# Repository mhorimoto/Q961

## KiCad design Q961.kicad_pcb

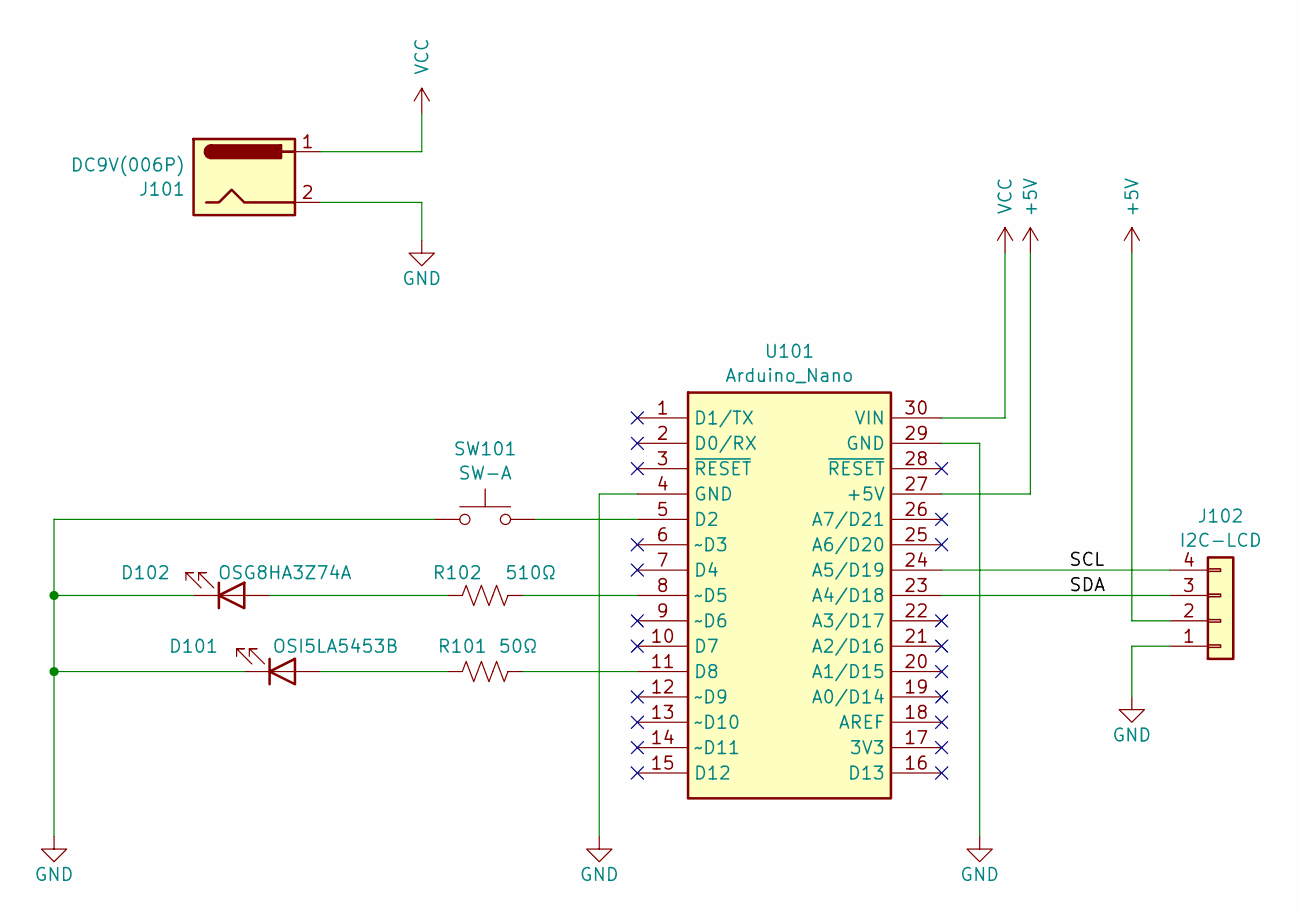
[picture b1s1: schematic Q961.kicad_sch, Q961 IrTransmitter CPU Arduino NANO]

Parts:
D101: OSI5LA5453B; LED_D5.0mm
D102: OSG8HA3Z74A; LED_D3.0mm
J101: DC9V(006P); BarrelJack_Horizontal
J102: I2C-LCD; JST_XH_B4B-XH-A_1x04_P2.50mm_Vertical
R101: 50Ω; R_Axial_DIN0204_L3.6mm_D1.6mm_P7.62mm_Horizontal
R102: 510Ω; R_Axial_DIN0204_L3.6mm_D1.6mm_P7.62mm_Horizontal
SW101: SW-A; TVDT18-050
U101: Arduino_Nano

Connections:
+5V: J102.2, U101.27 (+5V)
GND: D101.1 (K), D102.1 (K), J101.2, J102.1, SW101.1, U101.4 (GND), U101.29 (GND)
unnamed: D101.2 (A), R101.1
unnamed: D102.2 (A), R102.1
unnamed: J102.3, U101.23 (A4/D18)
unnamed: J102.4, U101.24 (A5/D19)
unnamed: SW101.2, U101.5 (D2)
unnamed: R101.2, U101.11 (D8)
unnamed: R102.2, U101.8 (~D5)
VCC: J101.1, U101.30 (VIN)

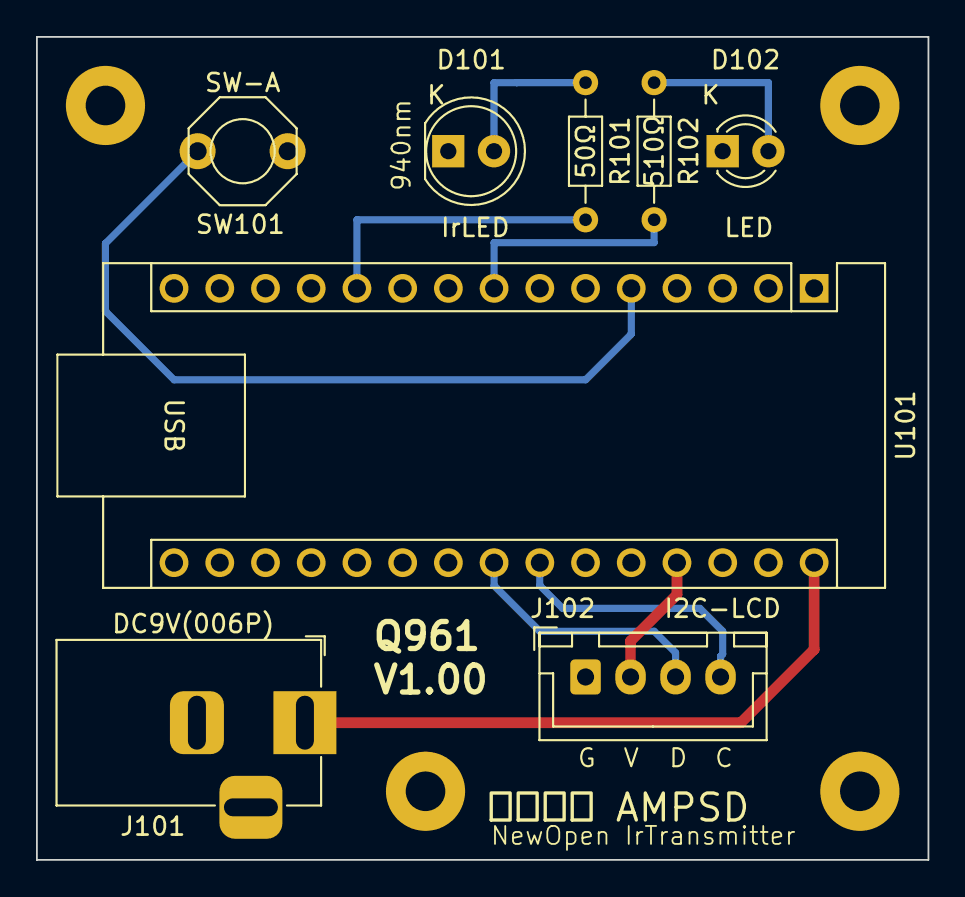
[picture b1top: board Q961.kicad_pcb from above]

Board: 2 copper layers, 49.5 x 45.7 mm, 8 parts (0 on the bottom side), 10 nets.

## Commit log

2024-09-23 1st commit
2025-08-17 KiCAD V9.0
